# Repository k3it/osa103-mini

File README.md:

# osa103-mini
Software Defined Multifunctional Measurment Device - VNA, Oscilloscope, Antenna Analyzer, Signal Generator, SDR trasceiver etc

- Some years ago, I entered the OSA103 schematic, published by the device's author, into KiCad, and routed and created the PCB. I was able to assemble the device and was in the process of debugging it. It was a personal project undertaken out of pure curiosity and to learn KiCad. Unfortunately, my vision started to deteriorate to the point where troubleshooting a small SMD board was no longer enjoyable, and I ultimately abandoned the project. I am releasing all of the files from the project directory, including the gerbers, in case someone finds them useful.

- All credit for the original device goes to the person named Sergey from Perm, Russia. You may be able to reach him via a forum on a site called cqham or https://www.osa103.ru (which seems to be down as of spring 2023).   I have no contacts with the forum since the start of the war in Feb 2022.  

- Please note that you may need to pay for a software license to use the official software for this board. I haven't kept up with the development, so use this project at your own risk. That being said, this is an ingenious and clever device, so have fun!

- I have no affiliation or contact with the author or the websites mentioned above, and I have no idea about the author's position regarding the ongoing invasion of Ukraine. However, I hope that the author stands against it, which seems to be the case with the majority of intelligent people. When you communicate with Sergey may be  you will be able clarify his stance.  Thank you

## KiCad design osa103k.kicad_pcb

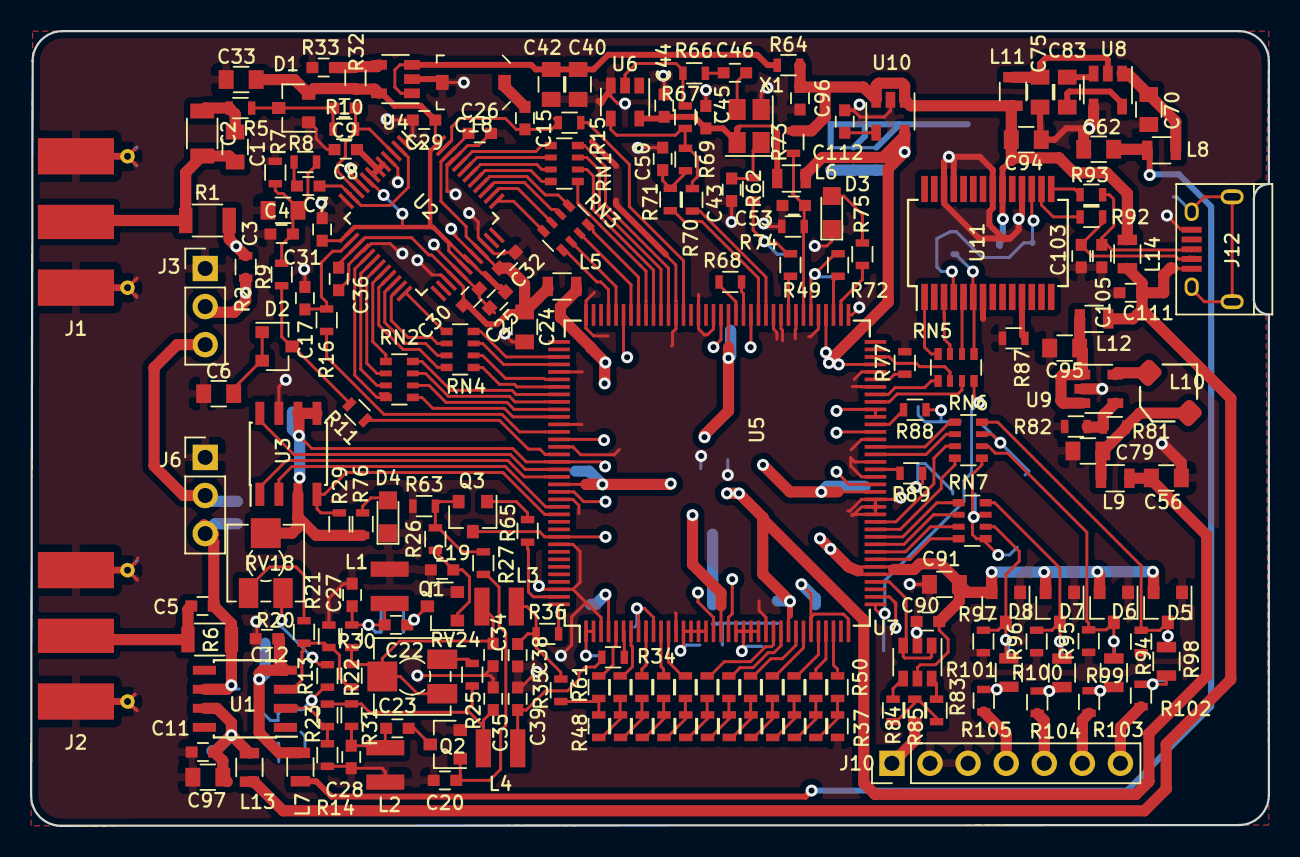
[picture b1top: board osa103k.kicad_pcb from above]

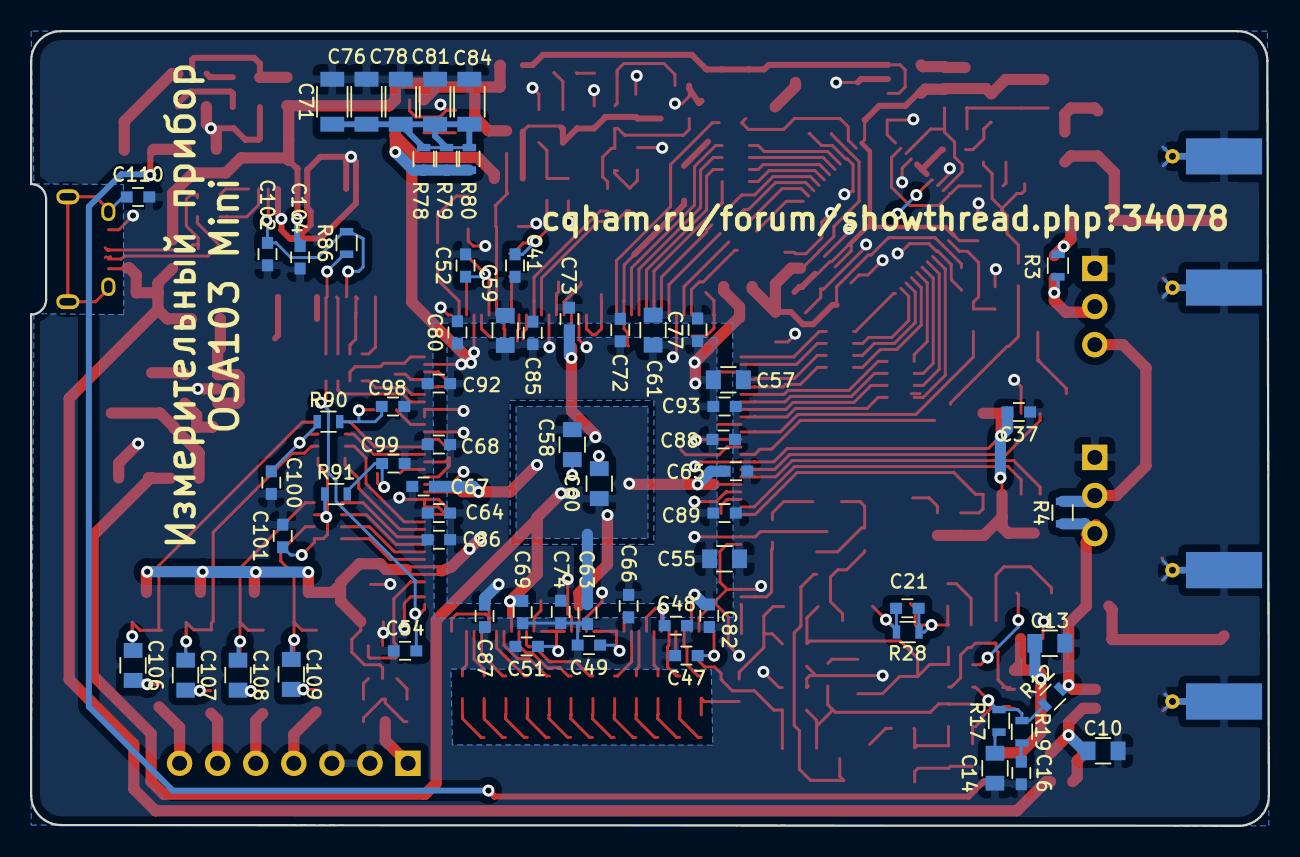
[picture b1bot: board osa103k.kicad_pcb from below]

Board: 2 copper layers, 82.5 x 53.0 mm, 267 parts (67 on the bottom side), 195 nets.

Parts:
C1, C6, C10, C13, C24, C33, C40, C42, C55, C56, C57, C58, C59, C60, C61, C62, C70, C75, C79, C83, C91, C94, C95, C97: 10uF; C_0805
C2, C71, C76, C78, C81, C84: 22uF; C_1206
C3, C15, C34, C35: 15p; C_0603
C4, C14: 470p; C_0805
C5, C38, C39: 2.2p; C_0603
C7, C8, C19, C20, C21, C22, C23, C30, C32, C37, C41, C43, C44, C45, C52, C63, C64, C65, C66, C67, C68, C69, C72, C73, C74, C77, C80, C82, C85, C86, C87, C88, C89, C90, C92, C93, C96, C98, C99, C100, C101, C104, C110, C111: 1uF; C_0603
C9, C16, C17, C54: NI; C_0603
C11, C12, C25, C26, C29, C31, C36, C46, C47, C48, C49, C50, C51, C53, C102: 0.1uF; C_0603
C18: 3..10p; C_Trimmer_Murata_TZC3
C27, C28: 6.2p; C_0603
C103, C105: 47p; C_0603
C106, C107, C108, C109: 3.6p; C_0805
C112: 10nF; C_0603
D1, D2, D5, D6, D7, D8: BAV99; SOT-23
D3: red; LED_0805
D4: green; LED_0805
J1, J2: Conn_Coaxial; Molex_SMA_Jack_Edge_Mount
J3, J6: Conn_01x03; Pin_Header_Straight_1x03_Pitch2.54mm
J10: Conn_01x07; Pin_Header_Straight_1x07_Pitch2.54mm
J12: USB_OTG; USB_Micro-B
L1, L2, L3, L4: 560n; Neosid_Inductor_SM-NE29_SMD1008
L5, L9, L12: BLM21PG221; R_0805
L6, L7, L8, L11, L13, L14: BLM21AG102; R_0805
L10: 10uH; CDRH3D16
Q1, Q2, Q3: BC846; SOT-23
R1, R6: 49.9 1%; R_1206
R2, R3, R35, R78, R79, R80: 1; R_0603
R4, R88, R89: 2k 1%; R_0603
R5, R10, R85: 10; R_0603
R7, R8, R15, R16, R71: 82; R_0603
R9, R12, R27, R63, R86: 910; R_0603
R11, R21: 270; R_0603
R13, R49, R62, R69, R72, R90, R91: 10k; R_0603
R14: 390; R_0603
R17, R20: 20k; R_0603
R19, R68: NI; R_0603
R22, R23: 200; R_0603
R25, R37, R50, R51, R52, R53, R54, R55, R56, R57, R58, R59, R60, R61, R102, R103, R104, R105: 470 1%; R_0603
R26, R30, R31, R34, R38, R39, R40, R41, R42, R43, R44, R45, R46, R47, R48, R65: 240 1%; R_0603
R28, R67: 2M; R_0603
R29, R75, R76, R82: 5.1k; R_0603
R32: 8.2k; R_0603
R33: 10nF; C_0603
R36, R73, R74, R94, R95, R96, R97: 24.9k 1%; R_0603
R64, R92, R93: 15; R_0603
R66, R70, R77, R83, R84, R87: 68; R_0603
R81: 7.5k; R_0603
R98, R99, R100, R101: 75k 1%; R_0805
RN1, RN2, RN3, RN4, RN5, RN6, RN7: 150; R_Array_Convex_4x0603
RV18: 20k; Potentiometer_Trimmer_Vishay_TS53YJ
RV24: 1k; Potentiometer_Trimmer_Vishay_TS53YJ
U1: AD8009ARZ; SOIC-8_3.9x4.9mm_Pitch1.27mm
U2: AD9288BST-40; LQFP-48_7x7mm_Pitch0.5mm
U3: AT45DB041D-SU; SOIC-8_3.9x4.9mm_Pitch1.27mm
U4: LP2985-1.8; SOT-23-5
U5: XC6SLXN-TQG144; TQFP-144_20x20mm_Pitch0.5mm
U6: 74LVC1GU04; SOT-23-5
U7: 74LVC2G14; SOT-23-6
U8: TPS60403_DBV_5; SOT-23-5
U9: TPS62200DBV; SOT-23-5
U10: LDK130-08_SOT23_SOT353; SOT-23-5
U11: FT232RL; SSOP-28_5.3x10.2mm_Pitch0.65mm
X1: VTCXO-14; Crystal_SMD_SeikoEpson_TSX3225-4pin_3.2x2.5mm

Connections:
+1.2V: C56.1, C58.1, C60.1, C63.1, C65.1, C67.1, C69.1, C73.1, L9.2, U5.19, U5.28, U5.52, U5.89, U5.128
+3.3USB: C102.2, R86.2, U11.4, U11.17
+3.3V: C37.2, C55.1, C57.1, C59.1, C61.1, C64.1, C66.1, C68.1, C72.1, C74.1, C77.1, C80.1, C82.1, C85.1, C86.1, C87.1, C88.1, C89.1, C90.2, C91.2, C92.1, C93.1, D5.2, D6.2, D7.2, D8.2, L5.1, L6.1, Q3.3, R29.2, R76.1, R78.2, R79.2, R80.2, RV18.2, U3.3, U3.5, U3.6, U5.4, U5.18, U5.20, U5.31, U5.36, U5.41, U5.42, U5.53, U5.60, U5.62, U5.63, U5.69, U5.76, U5.86, U5.90, U5.103, U5.122, U5.125, U5.129, U5.135, U7.5, U10.5
+5V: C94.1, C96.1, C104.1, L11.1, L14.2, R64.1, R73.1, U10.1, U10.3, U11.20
+5V_GEN: C10.1, C11.1, C97.1, L13.2, U1.7
+5_USB: C111.1, J12.1, L12.1, L13.1, L14.1
-5V_GEN: C12.1, C13.1, L7.2, U1.4
/osa103k Main/ADC0_0: RN3.5, U5.105
/osa103k Main/ADC0_1: RN3.6, U5.104
/osa103k Main/ADC0_2: RN3.7, U5.102
/osa103k Main/ADC0_3: RN3.8, U5.101
/osa103k Main/ADC0_4: RN1.5, U5.100
/osa103k Main/ADC0_5: RN1.6, U5.99
/osa103k Main/ADC0_6: RN1.7, U5.98
/osa103k Main/ADC0_7: RN1.8, U5.97
/osa103k Main/ADC1_0: RN4.8, U5.111
/osa103k Main/ADC1_1: RN4.7, U5.112
/osa103k Main/ADC1_2: RN4.6, U5.114
/osa103k Main/ADC1_3: RN4.5, U5.115
/osa103k Main/ADC1_4: RN2.8, U5.116
/osa103k Main/ADC1_5: RN2.7, U5.117
/osa103k Main/ADC1_6: RN2.6, U5.118
/osa103k Main/ADC1_7: RN2.5, U5.119
/osa103k Main/DAC_1: R50.2, U5.34
/osa103k Main/DAC_2: R51.2, U5.33
/osa103k Main/DAC_3: R52.2, U5.32
/osa103k Main/DAC_4: R53.2, U5.30
/osa103k Main/DAC_5: R54.2, U5.29
/osa103k Main/DAC_6: R55.2, U5.27
/osa103k Main/DAC_7: R56.2, U5.26
/osa103k Main/DAC_8: R57.2, U5.12
/osa103k Main/DAC_9: R58.2, U5.11
/osa103k Main/DAC_10: R59.2, U5.9
/osa103k Main/DAC_11: R60.2, U5.7
/osa103k Main/DAC_12: R61.2, U5.5
ADC0_ENC: R15.2, U5.95
ADC1_ENC: R16.2, U5.121
AUX_0: R68.2, U5.88
AUX_1: R68.1, U5.87
AUX_GEN: U5.40, U7.1, U7.3
CCK_RTS: RN5.6, U5.70
CH1_DITH: R11.1, U5.124
CH3N: RN7.8, U5.43
CH3P: RN7.7, U5.44
CH3_5_LEV: R89.2, U5.55
CH4N: RN7.6, U5.45
CH4P: RN7.5, U5.46
CH5N: RN6.8, U5.47
CH5P: RN6.7, U5.48
CH6N: RN6.6, U5.57
CH6P: RN6.5, U5.58
CH6_LEV: R88.2, U5.61
DAC144: R36.2, U5.144
DIN: RN5.5, U5.65
DOUT: RN5.7, U5.64
EE_CLK: U3.2, U5.131
EE_CS: R29.1, U3.4, U5.132
EE_SI: U3.1, U5.127
EE_SO: U3.8, U5.126
FREQ_ADJ: R49.1, U5.81
GEN_SINXX: R65.2, U5.143
GND: C3.1, C4.1, C6.1, C8.2, C10.2, C11.2, C12.2, C13.2, C14.2, C16.2, C17.1, C18.2, C19.2, C20.2, C24.2, C25.2, C26.2, C27.1, C28.2, C29.2, C30.2, C31.2, C32.2, C33.2, C34.2, C35.2, C36.2, C37.1, C38.2, C39.2, C40.2, C41.2, C42.2, C43.2, C44.2, C45.2, C47.2, C48.2, C49.2, C50.1, C51.2, C52.2, C53.2, C54.1, C55.2, C56.2, C57.2, C58.2, C59.2, C60.2, C61.2, C62.2, C63.2, C64.2, C65.2, C66.2, C67.2, C68.2, C69.2, C70.2, C71.2, C72.2, C73.2, C74.2, C75.2, C76.2, C77.2, C78.2, C79.2, C80.2, C81.2, C82.2, C84.2, C85.2, C86.2, C87.2, C88.2, C89.2, C90.1, C91.1, C92.2, C93.2, C94.2, C95.2, C96.2, C97.2, C98.2, C99.2, C100.2, C101.2, C102.1, C103.2, C104.2, C105.2, C110.2, C111.2, C112.1, D1.1, D3.1, D4.1, D5.1, D6.1, D7.1, D8.1, J1.2, J2.2, J3.1, J6.1, J10.2, J10.3, J12.5, L1.2, L2.1, Q1.2, Q2.2, R7.1, R14.1, R21.1, R33.2, R37.1, R63.1, R74.2, R77.2, R82.1, R87.1, R94.1, R95.1, R96.1, R97.1, U2.1, U2.4, U2.9, U2.12, U2.16, U2.27, U2.29, U2.32, U2.34, U2.45, U3.7, U4.2, U5.3, U5.13, U5.25, U5.38, U5.49, U5.50, U5.51, U5.54, U5.56, U5.59, U5.66, U5.68, U5.73, U5.77, U5.80, U5.82, U5.83, U5.91, U5.93, U5.96, U5.108, U5.113, U5.120, U5.123, U5.130, U5.136, U5.142, U6.3, U7.2, U8.4, U9.2, U10.2, U11.7, U11.18, U11.21, U11.25, U11.26, X1.2
LED_RED: R75.1, U5.74
MAIN_CLK: R71.2, U5.85
MAIN_CLKN: R70.2, U5.84
unnamed: C1.1, C2.1, R5.1
unnamed: C1.2, C2.2, J1.1, R1.1
unnamed: C3.2, C4.2, R7.2, R8.1, R9.2
unnamed: C5.1, J2.1, R6.2
unnamed: C5.2, J6.3, R4.1, R6.1, R12.2, U1.6
unnamed: C6.2, D2.1, D2.2
unnamed: C7.1, R8.2
unnamed: C7.2, U2.2, U2.11
unnamed: C8.1, U2.5, U2.6, U2.7
unnamed: C9.1, R10.2, U2.3, U2.10
unnamed: C9.2, D1.3, R5.2, R10.1
unnamed: C14.1, R17.1
unnamed: C15.1, C18.1
unnamed: C15.2, R15.1, U2.47
unnamed: C16.1, R19.1
unnamed: C17.2, R16.1, U2.14
unnamed: C19.1, Q1.1, R26.1
unnamed: C20.1, Q2.1, R27.1
unnamed: C21.1, C22.1, C27.2, L1.1, R28.2, R30.1
unnamed: C21.2, C22.2, Q1.3, R28.1
unnamed: C23.1, C28.1, L2.2, R31.1
unnamed: C23.2, Q2.3
unnamed: C34.1, L3.2, R22.2, R30.2, RV24.2, RV24.3
unnamed: C35.1, L4.2, R23.2, R25.1, R31.2
unnamed: C38.1, L3.1, R35.1, R36.1
unnamed: C39.1, L4.1, R34.1
unnamed: C40.1, C42.1, R64.2, U4.1, U4.3
unnamed: C41.1, R49.2, R62.1
unnamed: C43.1, R62.2, X1.1
unnamed: C46.1, R66.1
unnamed: C46.2, X1.3
unnamed: C47.1, U5.1, U5.2
unnamed: C48.1, U5.8, U5.10
unnamed: C49.1, U5.14, U5.15, U5.16, U5.17
unnamed: C50.2, R69.2, R71.1
unnamed: C51.1, U5.21, U5.22, U5.23, U5.24
unnamed: C62.1, L7.1, L8.2
unnamed: C70.1, L8.1, U8.1
unnamed: C71.1, C76.1, C78.1, C81.1, C84.1, R78.1, R79.1, R80.1
unnamed: C75.1, L11.2, U8.2
unnamed: C79.1, L9.1, L10.1, R81.2
unnamed: C83.1, U8.5
unnamed: C83.2, U8.3
unnamed: C95.1, L12.2, U9.1, U9.3
unnamed: C98.1, R88.1, R90.2
unnamed: C99.1, R89.1, R91.2
unnamed: C100.1, R90.1, RN6.3
unnamed: C101.1, R91.1, RN6.1, RN7.1, RN7.3
unnamed: C103.1, J12.2, R92.1
unnamed: C105.1, J12.3, R93.1
unnamed: C106.1, D5.3, R94.2, R98.2, RN6.4
unnamed: C106.2, R98.1, R102.2
unnamed: C107.1, D6.3, R95.2, R99.2, RN6.2
unnamed: C107.2, R99.1, R103.2
unnamed: C108.1, D7.3, R96.2, R100.2, RN7.4
unnamed: C108.2, R100.1, R104.2
unnamed: C109.1, D8.3, R97.2, R101.2, RN7.2
unnamed: C109.2, R101.1, R105.2
unnamed: C110.1, J12.6
unnamed: C112.2, U10.4
unnamed: D2.3, R9.1, R11.2
unnamed: D3.2, R75.2
unnamed: D4.2, R76.2
unnamed: J3.2, R2.2, R3.2
unnamed: J3.3, J6.2, R4.2
unnamed: J10.1, R85.1
unnamed: J10.4, R105.1
unnamed: J10.5, R104.1
unnamed: J10.6, R103.1
unnamed: J10.7, R102.1
unnamed: L10.2, U9.5
unnamed: Q3.1, R65.1
unnamed: R1.2, R2.1, R3.1
unnamed: R12.1, R13.1, R14.2, R17.2, R19.2, R23.1, U1.2
unnamed: R13.2, RV18.1
unnamed: R20.1, R21.2, R22.1, U1.3
unnamed: R20.2, RV18.3
unnamed: R25.2, RV24.1
unnamed: R32.1, R33.1, U4.4
unnamed: R34.2, U5.6
unnamed: R35.2, R48.2, R61.1
unnamed: R37.2, R38.1, R50.1
unnamed: R38.2, R39.1, R51.1
unnamed: R39.2, R40.1, R52.1
unnamed: R40.2, R41.1, R53.1
unnamed: R41.2, R42.1, R54.1
unnamed: R42.2, R43.1, R55.1
unnamed: R43.2, R44.1, R56.1
unnamed: R44.2, R45.1, R57.1
unnamed: R45.2, R46.1, R58.1
unnamed: R46.2, R47.1, R59.1
unnamed: R47.2, R48.1, R60.1
unnamed: R66.2, R67.1, U6.2
unnamed: R67.2, R69.1, R70.1, U6.4
unnamed: R77.1, U5.67
unnamed: R81.1, R82.2, U9.4
unnamed: R83.1, R84.1, R85.2
unnamed: R83.2, U7.6
unnamed: R84.2, U7.4
unnamed: R86.1, RN5.1, U11.6
unnamed: R87.2, U11.11
unnamed: R92.2, U11.16
unnamed: R93.2, U11.15
unnamed: RN1.1, U2.44
unnamed: RN1.2, U2.43
unnamed: RN1.3, U2.42
unnamed: RN1.4, U2.41
unnamed: RN2.1, U2.20
unnamed: RN2.2, U2.19
unnamed: RN2.3, U2.18
unnamed: RN2.4, U2.17
unnamed: RN3.1, U2.40
unnamed: RN3.2, U2.39
unnamed: RN3.3, U2.38
unnamed: RN3.4, U2.37
unnamed: RN4.1, U2.24
unnamed: RN4.2, U2.23
unnamed: RN4.3, U2.22
unnamed: RN4.4, U2.21
unnamed: RN5.2, U11.5
unnamed: RN5.3, U11.3
unnamed: RN5.4, U11.1
PROG_B: C54.2, RN5.8, U5.37
SINXX_B: Q3.2, R26.2, R27.2, R63.2
VCC: C44.1, C45.1, L6.2, U6.5, X1.4
VCC_CMP_LEV: R72.1, U5.75
VCC_CMP_N: C52.1, R72.2, U5.78
VCC_CMP_P: C53.1, R73.2, R74.1, U5.79
VD+3.3: C25.1, C29.1, C31.1, C33.1, D1.2, R32.2, U2.8, U2.13, U2.30, U2.31, U2.48, U4.5
VDD+3.3: C24.1, C26.1, C30.1, C32.1, C36.1, L5.2, U2.15, U2.28, U2.33, U2.46

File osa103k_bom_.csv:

Component,Description,Part,References,Value,Footprint,Quantity Per PCB,Datasheet
1,Unpolarized capacitor,C,C11 C12 C25 C26 C29 C31 C36 C46 C47 C48 C49 C50 C51 C53 C102,0.1uF,C_0603,15,
2,Unpolarized capacitor,C,C112 R33,10nF,C_0603,2,
3,Unpolarized capacitor,C,C1 C6 C10 C13 C24 C33 C40 C42 C55 C56 C57 C58 C59 C60 C61 C62 C70 C75 C79 C83 C91 C94 C95 C97,10uF,C_0805,24,
4,Unpolarized capacitor,C,C3 C15 C34 C35,15p,C_0603,4,
5,Unpolarized capacitor,C,C7 C8 C19 C20 C21 C22 C23 C30 C32 C37 C41 C43 C44 C45 C52 C63 C64 C65 C66 C67 C68 C69 C72 C73 C74 C77 C80 C82 C85 C86 C87 C88 C89 C90 C92 C93 C96 C98 C99 C100 C101 C104 C110 C111,1uF,C_0603,44,
6,Unpolarized capacitor,C,C5 C38 C39,2.2p,C_0603,3,
7,Unpolarized capacitor,C,C2 C71 C76 C78 C81 C84,22uF,C_1206,6,
8,Variable capacitor,C_Variable,C18,3..10p,C_Trimmer_Murata_TZC3,1,
9,Unpolarized capacitor,C,C106 C107 C108 C109,3.6p,C_0805,4,
10,Unpolarized capacitor,C,C4 C14,470p,C_0805,2,
11,Unpolarized capacitor,C,C103 C105,47p,C_0603,2,
12,Unpolarized capacitor,C,C27 C28,6.2p,C_0603,2,
13,Unpolarized capacitor,C,C9 C16 C17 C54,NI,C_0603,4,
14,BAV99 High-speed switching diodes,BAV99,D1 D2 D5 D6 D7 D8,BAV99,SOT-23,6,www.nxp.com/documents/data_sheet/BAV99_SER.pdf
15,LED generic,LED,D4,green,LED_0805,1,
16,LED generic,LED,D3,red,LED_0805,1,
17,"Generic connector, single row, 01x03",Conn_01x03,J3 J6,Conn_01x03,Pin_Header_Straight_1x03_Pitch2.54mm,2,
18,"Generic connector, single row, 01x07",Conn_01x07,J10,Conn_01x07,Pin_Header_Straight_1x07_Pitch2.54mm,1,
19,"coaxial connector (BNC, SMA, SMB, SMC, Cinch/RCA, ...)",Conn_Coaxial,J1 J2,Conn_Coaxial,Molex_SMA_Jack_Edge_Mount,2,
20,USB mini/micro connector,USB_OTG,J12,USB_OTG,USB_Micro-B,1,
21,Inductor,L,L10,10uH,CDRH3D16,1,
22,Inductor,L,L1 L2 L3 L4,560n,Neosid_Inductor_SM-NE29_SMD1008,4,
23,"Ferrite bead, small symbol",Ferrite_Bead_Small,L6 L7 L8 L11 L13 L14,BLM21AG102,R_0805,6,
24,"Ferrite bead, small symbol",Ferrite_Bead_Small,L5 L9 L12,BLM21PG221,R_0805,3,
25,"45V Vce, 0.8A Ic, NPN, SOT-23",BC817,Q1 Q2 Q3,BC846,SOT-23,3,http://www.fairchildsemi.com/ds/BC/BC817.pdf
26,Resistor,R,R2 R3 R35 R78 R79 R80,1,R_0603,6,
27,Resistor,R,R5 R10 R85,10,R_0603,3,
28,Resistor,R,R49 R62 R69 R72 R90 R91,10k,R_0603,6,
29,Resistor,R,R64 R92 R93,15,R_0603,3,
30,Resistor,R,R22 R23,200,R_0603,2,
31,Resistor,R,R13 R17 R20,20k,R_0603,3,
32,Resistor,R,R36 R73 R74 R94 R95 R96 R97,24.9k 1%,R_0603,7,
33,Resistor,R,R26 R30 R31 R34 R38 R39 R40 R41 R42 R43 R44 R45 R46 R47 R48 R65,240 1%,R_0603,16,
34,Resistor,R,R11 R21,270,R_0603,2,
35,Resistor,R,R28 R67,2M,R_0603,2,
36,Resistor,R,R4 R88 R89,2k 1%,R_0603,3,
37,Resistor,R,R14,390,R_0603,1,
38,Resistor,R,R25 R37 R50 R51 R52 R53 R54 R55 R56 R57 R58 R59 R60 R61 R102 R103 R104 R105,470 1%,R_0603,18,
39,Resistor,R,R1 R6,49.9 1%,R_1206,2,
40,Resistor,R,R29 R75 R76 R82,5.1k,R_0603,4,
41,Resistor,R,R66 R70 R77 R83 R84 R87,68,R_0603,6,
42,Resistor,R,R81,7.5k,R_0603,1,
43,Resistor,R,R98 R99 R100 R101,75k 1%,R_0805,4,
44,Resistor,R,R32,8.2k,R_0603,1,
45,Resistor,R,R7 R8 R15 R16 R71,82,R_0603,5,
46,Resistor,R,R9 R12 R27 R63 R86,910,R_0603,5,
47,Resistor,R,R19 R68,NI,R_0603,2,
48,"4 Resistor network, parallel topology, DIP package",R_Pack04,RN1 RN2 RN3 RN4 RN5 RN6 RN7,150,R_Array_Convex_4x0603,7,
49,Potentiometer,POT,RV24,1k,Potentiometer_Trimmer_Vishay_TS53YJ,1,
50,Potentiometer,POT,RV18,20k,Potentiometer_Trimmer_Vishay_TS53YJ,1,
51,"Single NOT Gate, Low-Voltage CMOS",74LVC1G04,U6,74LVC1GU04,SOT-23-5,1,http://www.ti.com/lit/sg/scyt129e/scyt129e.pdf
52,"Dual NOT Gate Schmidt Triggered, Low-Voltage CMOS",74LVC2G14,U7,74LVC2G14,SOT-23-6,1,http://www.ti.com/lit/sg/scyt129e/scyt129e.pdf
53,,AD8009ARZ,U1,AD8009ARZ,SOIC-8_3.9x4.9mm_Pitch1.27mm,1,
54,,AD9288BST-100,U2,AD9288BST-40,LQFP-48_7x7mm_Pitch0.5mm,1,
55,,AT45DB041D-SU,U3,AT45DB041D-SU,SOIC-8_3.9x4.9mm_Pitch1.27mm,1,
56,"USB to Serial Interface, SSOP-28",FT232RL,U11,FT232RL,SSOP-28_5.3x10.2mm_Pitch0.65mm,1,http://www.ftdichip.com/Products/ICs/FT232RL.htm
57,"300mA low dropout linear regulator, low quiescent current very, low noise, shutdown pin, 0.8V fixed positive output, SOT-23-5/SOT-353-5/SC-70-5",LDK130-08_SOT23_SOT353,U10,LDK130-08_SOT23_SOT353,SOT-23-5,1,http://www.st.com/content/ccc/resource/technical/document/da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
58,"150mA 16V Low-noise Low-dropout Regulator With Shutdown, 1.8V output voltage, SOT-23-5",LP2985-1.8,U4,LP2985-1.8,SOT-23-5,1,http://www.ti.com/lit/ds/symlink/lp2985.pdf
59,,TPS60403_DBV_5,U8,TPS60403_DBV_5,SOT-23-5,1,
60,"SOT-23-5, High-Efficiency Step-Down DC-DC Converter, Adjustable",TPS62200DBV,U9,TPS62200DBV,SOT-23-5,1,http://www.ti.com/lit/ds/symlink/tps62201.pdf
61,,XC6SLXN-TQG144,U5,XC6SLXN-TQG144,TQFP-144_20x20mm_Pitch0.5mm,1,
62,"Voltage-Controlled Crystal Clock Oscillator, DIP14-style metal package",VTCXO-14,X1,VTCXO-14,Crystal_SMD_SeikoEpson_TSX3225-4pin_3.2x2.5mm,1,http://www.golledge.com/pdf/products/tcxos/gtxos14.pdf





Component Groups:,62
Component Count:,267
Fitted Components:,267
Number of PCBs:,1
Total components:,267
Schematic Version:,
Schematic Date:,
BoM Date:,31/01/2018 22:51:36
Schematic Source:,C:\Users\uncle_ziba\Documents\Dropbox\kicad\osa103-kl\osa103k\osa103k.sch
KiCad Version:,Eeschema (2018-01-26 revision 0d532b43d)-makepkg

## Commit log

2023-03-20 Publish KiCad project and gerber files
2023-03-20 create top level directory
